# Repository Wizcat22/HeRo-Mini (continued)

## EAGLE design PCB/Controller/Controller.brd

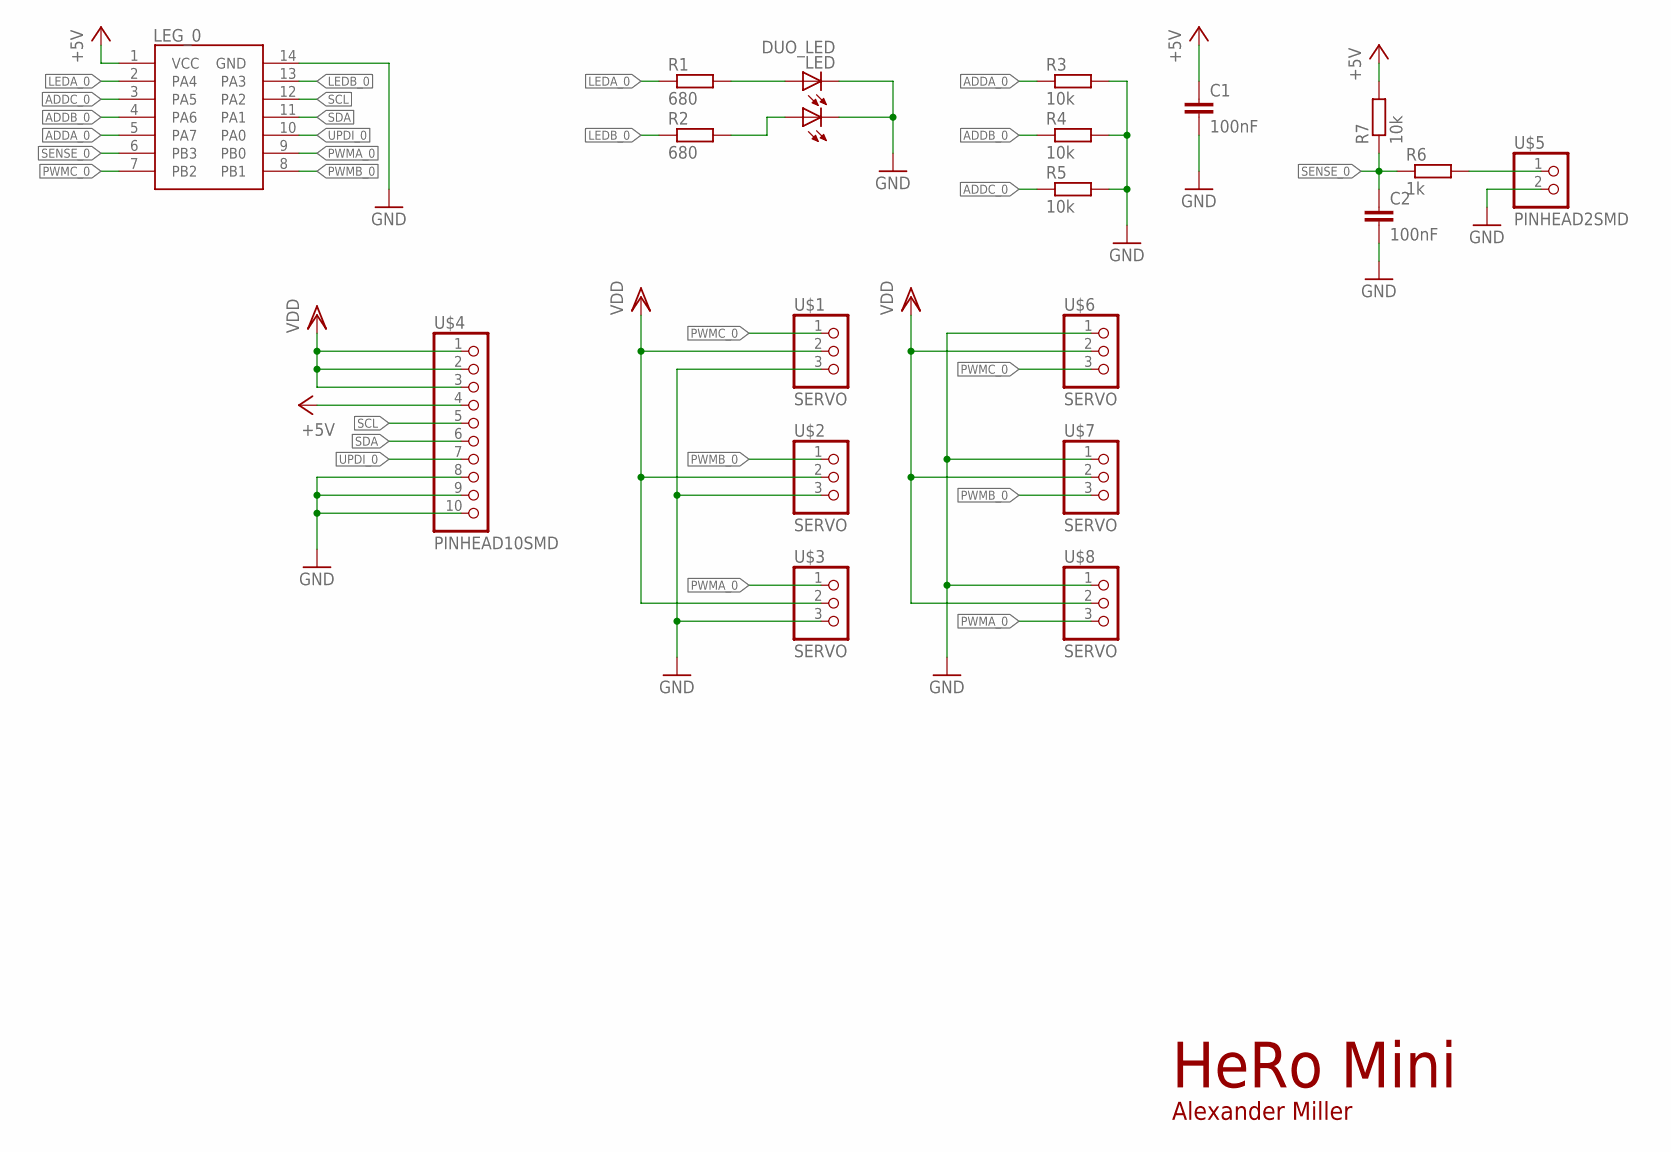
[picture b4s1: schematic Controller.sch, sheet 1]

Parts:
C1, C2: 100nF; C0805
LED: DUO_LED
LEG_0: ATTINY16142; SOIC127P600X175-14
R1, R2: 680; R0805
R3, R4, R5, R7: 10k; R0805
R6: 1k; R0805
U$1, U$2, U$3, U$6, U$7, U$8: SERVO; SL12SMD058
U$4: PINHEAD10SMD; PINHD10SMD
U$5: PINHEAD2SMD; PINHD2SMD

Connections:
+5V: C1.1, LEG_0.1 (VCC), R7.2, U$4.4
ADDA_0: LEG_0.5 (PA7), R3.1
ADDB_0: LEG_0.4 (PA6), R4.1
ADDC_0: LEG_0.3 (PA5), R5.1
GND: C1.2, C2.2, LED.CG, LED.CR, LEG_0.14 (GND), R3.2, R4.2, R5.2, U$1.3, U$2.3, U$3.3, U$4.8, U$4.9, U$4.10, U$5.2, U$6.1, U$7.1, U$8.1
LEDA_0: LEG_0.2 (PA4), R1.1
LEDB_0: LEG_0.13 (PA3), R2.1
unnamed: LED.AG, R1.2
unnamed: LED.AR, R2.2
unnamed: R6.2, U$5.1
PWMA_0: LEG_0.9 (PB0), U$3.1, U$8.3
PWMB_0: LEG_0.8 (PB1), U$2.1, U$7.3
PWMC_0: LEG_0.7 (PB2), U$1.1, U$6.3
SCL: LEG_0.12 (PA2), U$4.5
SDA: LEG_0.11 (PA1), U$4.6
SENSE_0: C2.1, LEG_0.6 (PB3), R6.1, R7.1
UPDI_0: LEG_0.10 (PA0), U$4.7
VDD: U$1.2, U$2.2, U$3.2, U$4.1, U$4.2, U$4.3, U$6.2, U$7.2, U$8.2

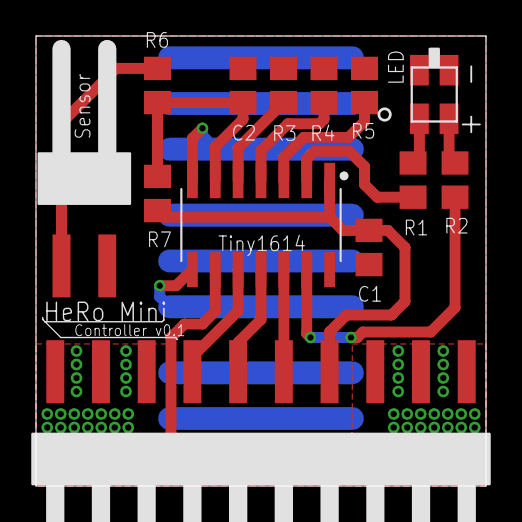
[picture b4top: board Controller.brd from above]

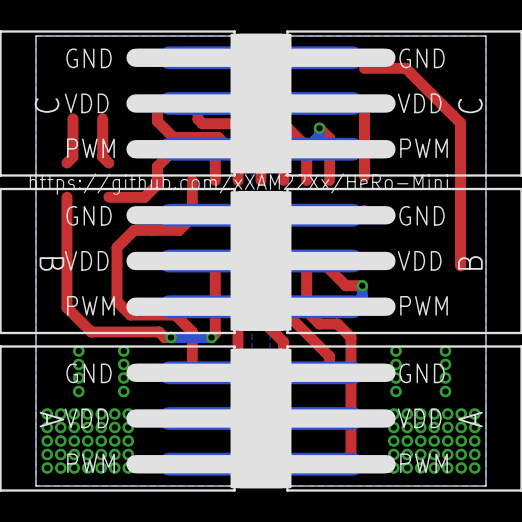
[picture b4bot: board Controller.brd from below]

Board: 2 copper layers, 25.0 x 25.0 mm, 19 parts (6 on the bottom side), 18 nets.

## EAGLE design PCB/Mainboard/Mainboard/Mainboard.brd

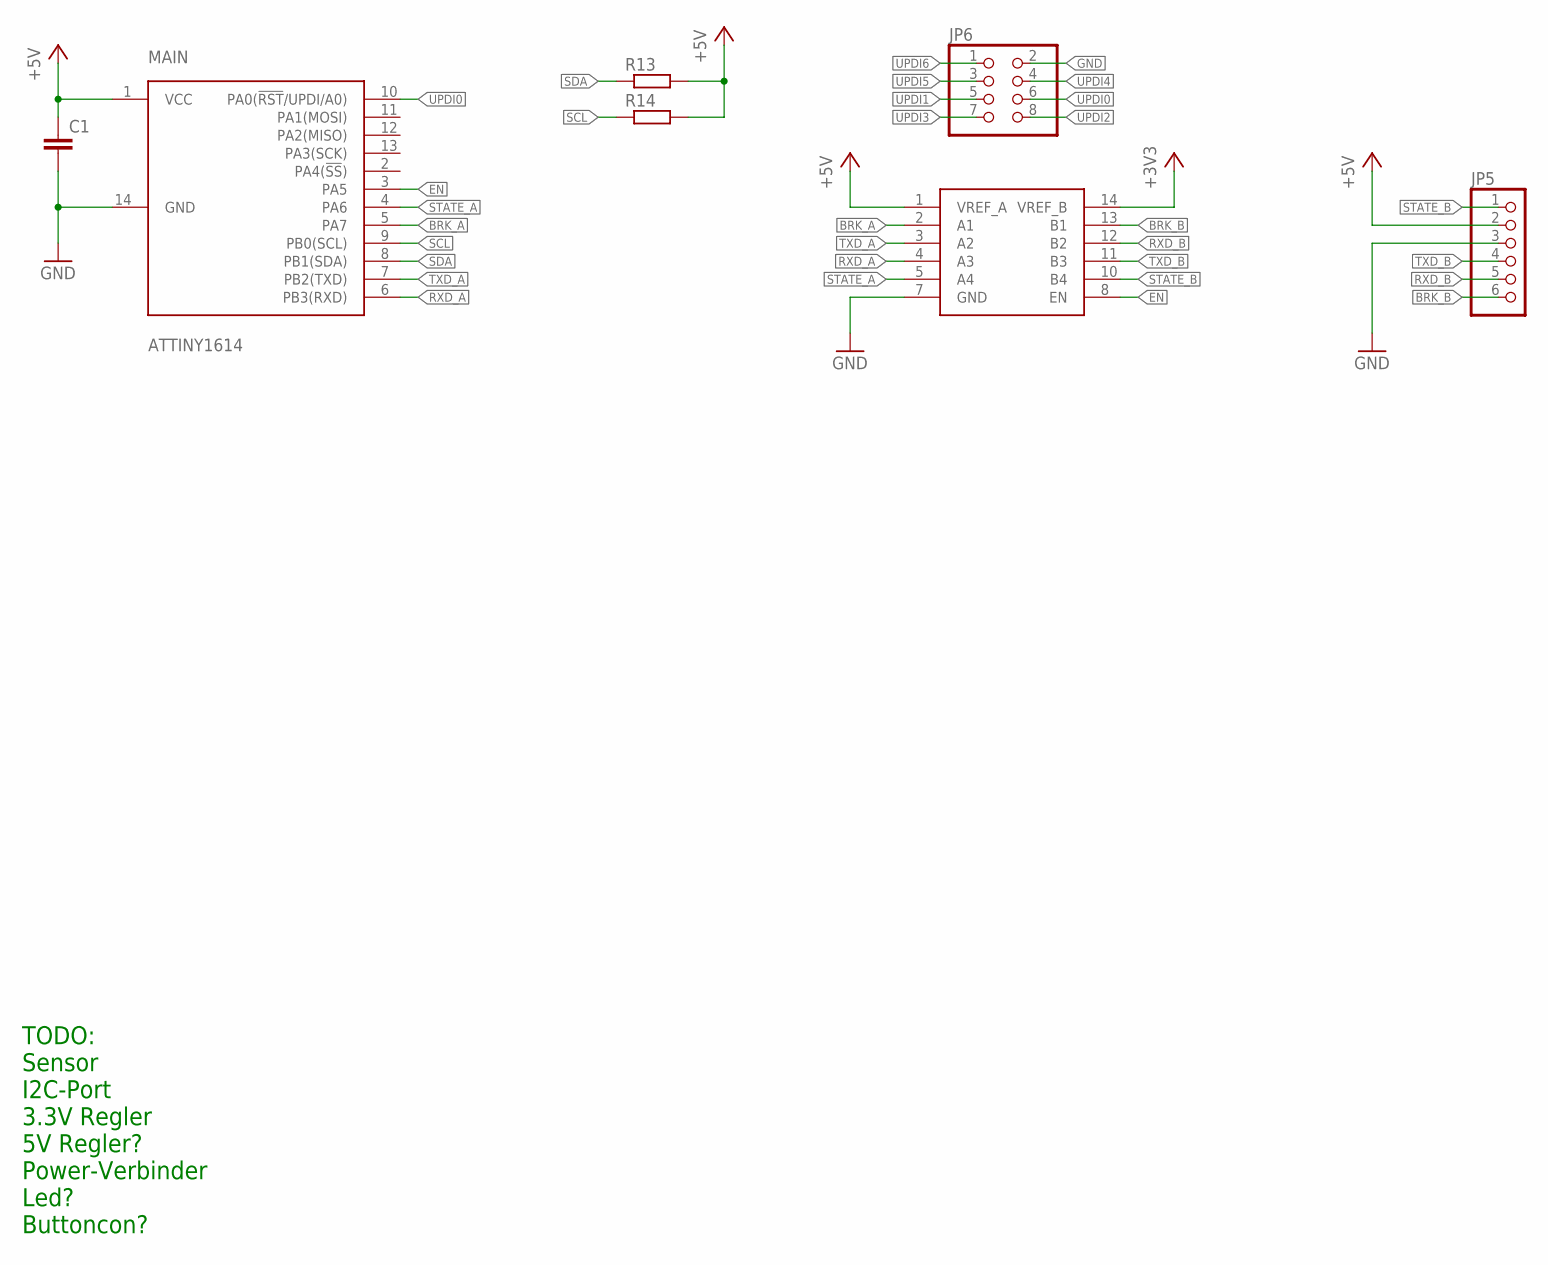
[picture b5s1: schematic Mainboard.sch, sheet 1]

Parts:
C1: C-EUC0805; C0805
JP5: PINHD-1X6; 1X06
JP6: PINHD-2X4; 2X04
MAIN: ATTINY1614; SOIC14
R13, R14: R-EU_R0805; R0805
U$2: LSF0204; TSSOP14

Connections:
+3V3: U$2.14 (VREF_B)
+5V: C1.1, JP5.2, MAIN.1 (VCC), R13.2, R14.2, U$2.1 (VREF_A); also elsewhere on the board
BRK_A: MAIN.5 (PA7), U$2.2 (A1)
BRK_B: JP5.6, U$2.13 (B1)
EN: MAIN.3 (PA5), U$2.8 (EN)
GND: C1.2, JP5.3, JP6.2, MAIN.14 (GND), U$2.7 (GND); also elsewhere on the board
RXD_A: MAIN.6 (PB3(RXD)), U$2.4 (A3)
RXD_B: JP5.5, U$2.12 (B2)
SCL: MAIN.9 (PB0(SCL)), R14.1; also elsewhere on the board
SDA: MAIN.8 (PB1(SDA)), R13.1; also elsewhere on the board
STATE_A: MAIN.4 (PA6), U$2.5 (A4)
STATE_B: JP5.1, U$2.10 (B4)
TXD_A: MAIN.7 (PB2(TXD)), U$2.3 (A2)
TXD_B: JP5.4, U$2.11 (B3)
UPDI0: JP6.6, MAIN.10 (PA0(!RST!/UPDI/A0))
UPDI1: JP6.5; also elsewhere on the board
UPDI2: JP6.8; also elsewhere on the board
UPDI3: JP6.7; also elsewhere on the board
UPDI4: JP6.4; also elsewhere on the board
UPDI5: JP6.3; also elsewhere on the board
UPDI6: JP6.1; also elsewhere on the board

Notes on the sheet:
TODO: Sensor I2C-Port 3.3V Regler 5V Regler? Power-Verbinder Led? Buttoncon?

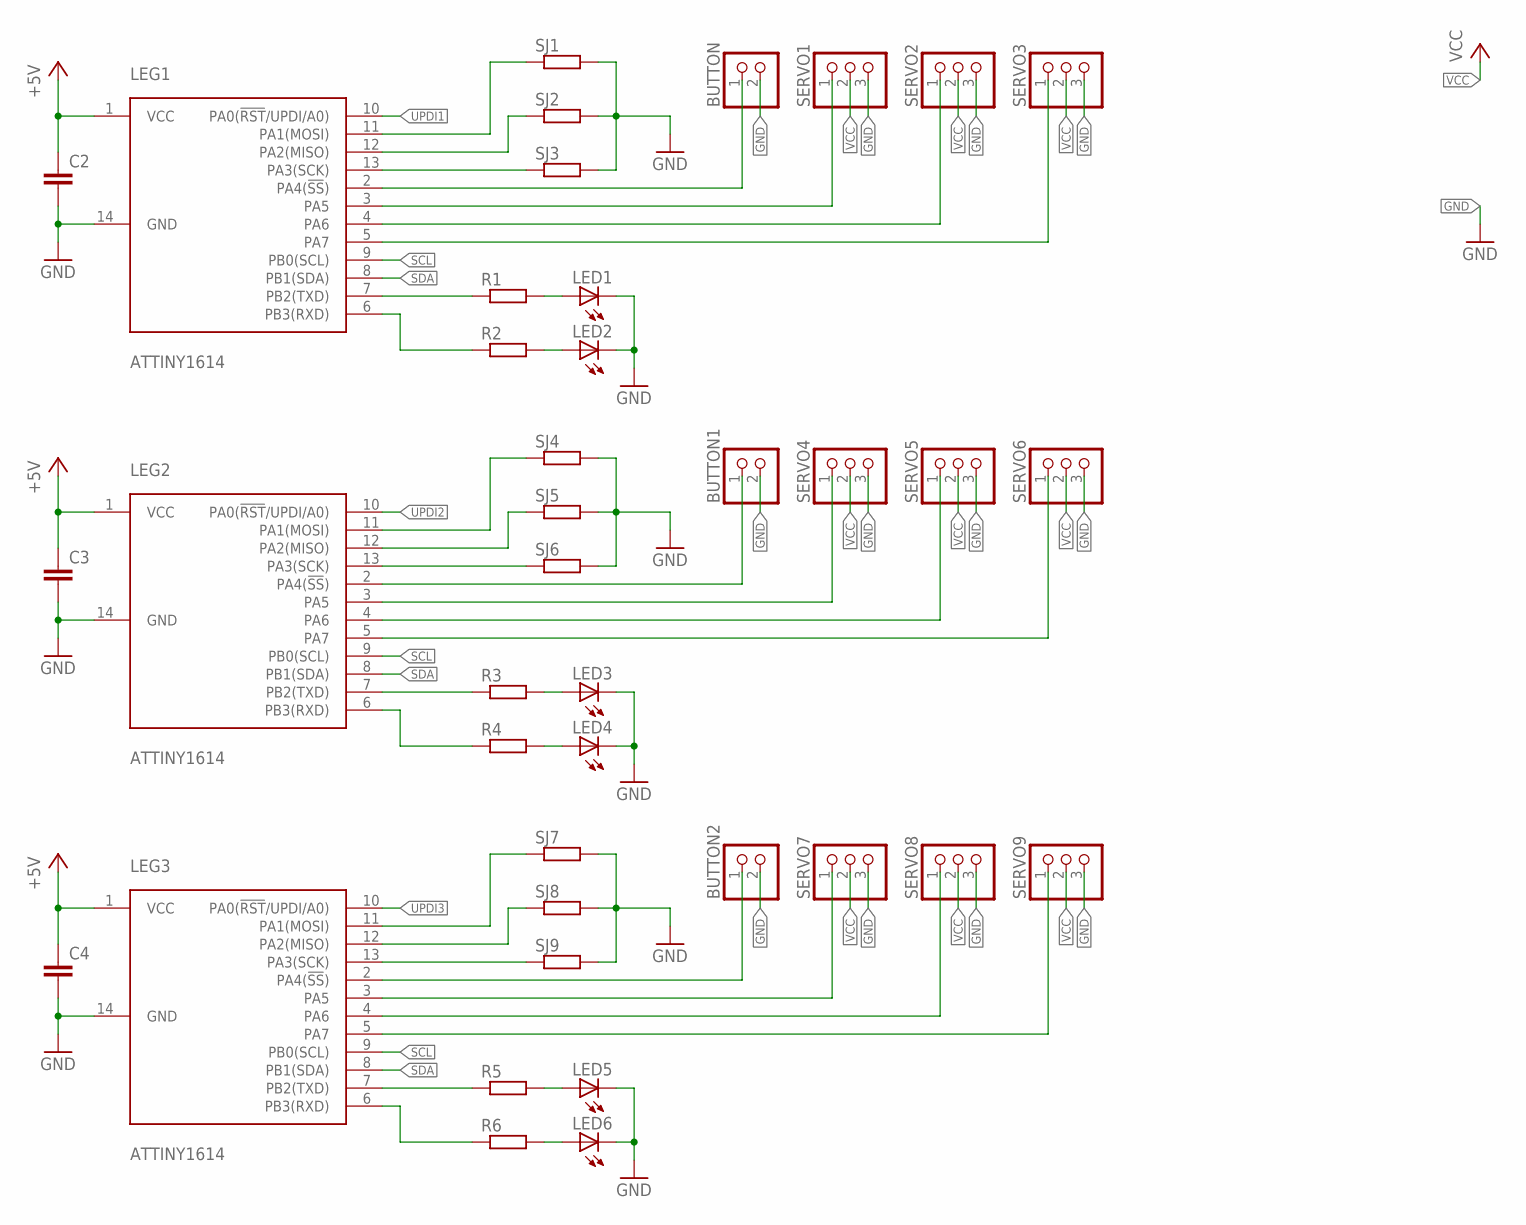
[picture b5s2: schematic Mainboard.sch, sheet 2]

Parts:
BUTTON, BUTTON1, BUTTON2: PINHD-1X2; 1X02
C2, C3, C4: C-EUC0805; C0805
LED1, LED2, LED3, LED4, LED5, LED6: LEDCHIP-LED0805; CHIP-LED0805
LEG1, LEG2, LEG3: ATTINY1614; SOIC14
R1, R2, R3, R4, R5, R6: R-EU_R0805; R0805
SERVO1, SERVO2, SERVO3, SERVO4, SERVO5, SERVO6, SERVO7, SERVO8, SERVO9: PINHD-1X3; 1X03
SJ1, SJ2, SJ3, SJ4, SJ5, SJ6, SJ7, SJ8, SJ9: R-EU_R0402; R0402

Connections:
+5V: C2.1, C3.1, C4.1, LEG1.1 (VCC), LEG2.1 (VCC), LEG3.1 (VCC); also elsewhere on the board
GND: BUTTON.2, BUTTON1.2, BUTTON2.2, C2.2, C3.2, C4.2, LED1.C, LED2.C, LED3.C, LED4.C, LED5.C, LED6.C, LEG1.14 (GND), LEG2.14 (GND), LEG3.14 (GND), SERVO1.3, SERVO2.3, SERVO3.3, SERVO4.3, SERVO5.3, SERVO6.3, SERVO7.3, SERVO8.3, SERVO9.3, SJ1.2, SJ2.2, SJ3.2, SJ4.2, SJ5.2, SJ6.2, SJ7.2, SJ8.2, SJ9.2; also elsewhere on the board
unnamed: LEG1.7 (PB2(TXD)), R1.1
unnamed: LEG1.6 (PB3(RXD)), R2.1
unnamed: LEG1.11 (PA1(MOSI)), SJ1.1
unnamed: LEG1.12 (PA2(MISO)), SJ2.1
unnamed: LEG1.13 (PA3(SCK)), SJ3.1
unnamed: LED1.A, R1.2
unnamed: LED2.A, R2.2
unnamed: BUTTON.1, LEG1.2 (PA4(!SS!))
unnamed: LEG1.3 (PA5), SERVO1.1
unnamed: LEG1.4 (PA6), SERVO2.1
unnamed: LED3.A, R3.2
unnamed: LEG1.5 (PA7), SERVO3.1
unnamed: LED4.A, R4.2
unnamed: LEG2.7 (PB2(TXD)), R3.1
unnamed: LEG2.6 (PB3(RXD)), R4.1
unnamed: LEG2.11 (PA1(MOSI)), SJ4.1
unnamed: LEG2.12 (PA2(MISO)), SJ5.1
unnamed: LEG2.13 (PA3(SCK)), SJ6.1
unnamed: BUTTON1.1, LEG2.2 (PA4(!SS!))
unnamed: LEG2.3 (PA5), SERVO4.1
unnamed: LEG2.4 (PA6), SERVO5.1
unnamed: LEG2.5 (PA7), SERVO6.1
unnamed: LED5.A, R5.2
unnamed: LED6.A, R6.2
unnamed: LEG3.7 (PB2(TXD)), R5.1
unnamed: LEG3.6 (PB3(RXD)), R6.1
unnamed: LEG3.11 (PA1(MOSI)), SJ7.1
unnamed: LEG3.12 (PA2(MISO)), SJ8.1
unnamed: LEG3.13 (PA3(SCK)), SJ9.1
unnamed: BUTTON2.1, LEG3.2 (PA4(!SS!))
unnamed: LEG3.3 (PA5), SERVO7.1
unnamed: LEG3.4 (PA6), SERVO8.1
unnamed: LEG3.5 (PA7), SERVO9.1
SCL: LEG1.9 (PB0(SCL)), LEG2.9 (PB0(SCL)), LEG3.9 (PB0(SCL)); also elsewhere on the board
SDA: LEG1.8 (PB1(SDA)), LEG2.8 (PB1(SDA)), LEG3.8 (PB1(SDA)); also elsewhere on the board
UPDI1: LEG1.10 (PA0(!RST!/UPDI/A0)); also elsewhere on the board
UPDI2: LEG2.10 (PA0(!RST!/UPDI/A0)); also elsewhere on the board
UPDI3: LEG3.10 (PA0(!RST!/UPDI/A0)); also elsewhere on the board
VCC: SERVO1.2, SERVO2.2, SERVO3.2, SERVO4.2, SERVO5.2, SERVO6.2, SERVO7.2, SERVO8.2, SERVO9.2

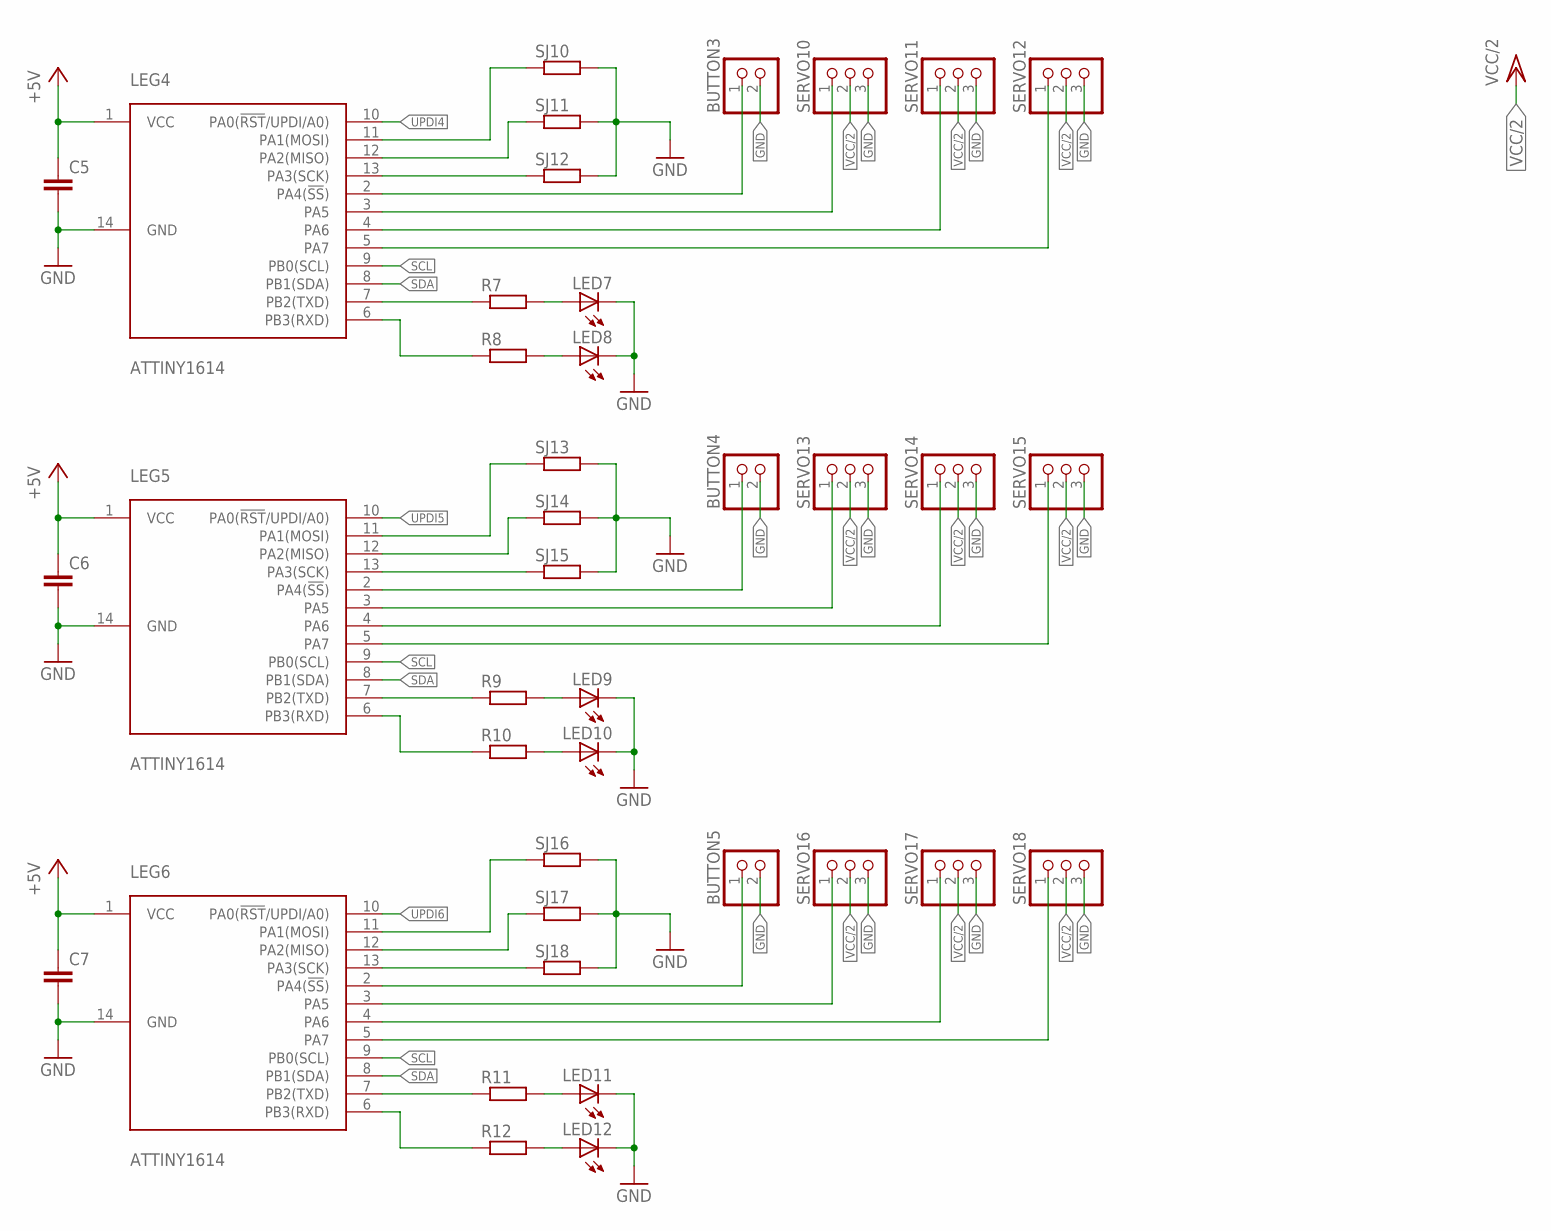
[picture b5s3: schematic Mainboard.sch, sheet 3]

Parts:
BUTTON3, BUTTON4, BUTTON5: PINHD-1X2; 1X02
C5, C6, C7: C-EUC0805; C0805
LED7, LED8, LED9, LED10, LED11, LED12: LEDCHIP-LED0805; CHIP-LED0805
LEG4, LEG5, LEG6: ATTINY1614; SOIC14
R7, R8, R9, R10, R11, R12: R-EU_R0805; R0805
SERVO10, SERVO11, SERVO12, SERVO13, SERVO14, SERVO15, SERVO16, SERVO17, SERVO18: PINHD-1X3; 1X03
SJ10, SJ11, SJ12, SJ13, SJ14, SJ15, SJ16, SJ17, SJ18: R-EU_R0402; R0402

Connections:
+5V: C5.1, C6.1, C7.1, LEG4.1 (VCC), LEG5.1 (VCC), LEG6.1 (VCC); also elsewhere on the board
GND: BUTTON3.2, BUTTON4.2, BUTTON5.2, C5.2, C6.2, C7.2, LED7.C, LED8.C, LED9.C, LED10.C, LED11.C, LED12.C, LEG4.14 (GND), LEG5.14 (GND), LEG6.14 (GND), SERVO10.3, SERVO11.3, SERVO12.3, SERVO13.3, SERVO14.3, SERVO15.3, SERVO16.3, SERVO17.3, SERVO18.3, SJ10.2, SJ11.2, SJ12.2, SJ13.2, SJ14.2, SJ15.2, SJ16.2, SJ17.2, SJ18.2; also elsewhere on the board
unnamed: LED7.A, R7.2
unnamed: LED8.A, R8.2
unnamed: LEG4.7 (PB2(TXD)), R7.1
unnamed: LEG4.6 (PB3(RXD)), R8.1
unnamed: LEG4.11 (PA1(MOSI)), SJ10.1
unnamed: LEG4.12 (PA2(MISO)), SJ11.1
unnamed: LEG4.13 (PA3(SCK)), SJ12.1
unnamed: BUTTON3.1, LEG4.2 (PA4(!SS!))
unnamed: LEG4.3 (PA5), SERVO10.1
unnamed: LEG4.4 (PA6), SERVO11.1
unnamed: LEG4.5 (PA7), SERVO12.1
unnamed: LED9.A, R9.2
unnamed: LED10.A, R10.2
unnamed: LEG5.7 (PB2(TXD)), R9.1
unnamed: LEG5.6 (PB3(RXD)), R10.1
unnamed: LEG5.11 (PA1(MOSI)), SJ13.1
unnamed: LEG5.12 (PA2(MISO)), SJ14.1
unnamed: LEG5.13 (PA3(SCK)), SJ15.1
unnamed: BUTTON4.1, LEG5.2 (PA4(!SS!))
unnamed: LEG5.3 (PA5), SERVO13.1
unnamed: LEG5.4 (PA6), SERVO14.1
unnamed: LEG5.5 (PA7), SERVO15.1
unnamed: LED11.A, R11.2
unnamed: LED12.A, R12.2
unnamed: LEG6.7 (PB2(TXD)), R11.1
unnamed: LEG6.6 (PB3(RXD)), R12.1
unnamed: LEG6.11 (PA1(MOSI)), SJ16.1
unnamed: LEG6.12 (PA2(MISO)), SJ17.1
unnamed: LEG6.13 (PA3(SCK)), SJ18.1
unnamed: BUTTON5.1, LEG6.2 (PA4(!SS!))
unnamed: LEG6.3 (PA5), SERVO16.1
unnamed: LEG6.4 (PA6), SERVO17.1
unnamed: LEG6.5 (PA7), SERVO18.1
SCL: LEG4.9 (PB0(SCL)), LEG5.9 (PB0(SCL)), LEG6.9 (PB0(SCL)); also elsewhere on the board
SDA: LEG4.8 (PB1(SDA)), LEG5.8 (PB1(SDA)), LEG6.8 (PB1(SDA)); also elsewhere on the board
UPDI4: LEG4.10 (PA0(!RST!/UPDI/A0)); also elsewhere on the board
UPDI5: LEG5.10 (PA0(!RST!/UPDI/A0)); also elsewhere on the board
UPDI6: LEG6.10 (PA0(!RST!/UPDI/A0)); also elsewhere on the board
VCC/2: SERVO10.2, SERVO11.2, SERVO12.2, SERVO13.2, SERVO14.2, SERVO15.2, SERVO16.2, SERVO17.2, SERVO18.2

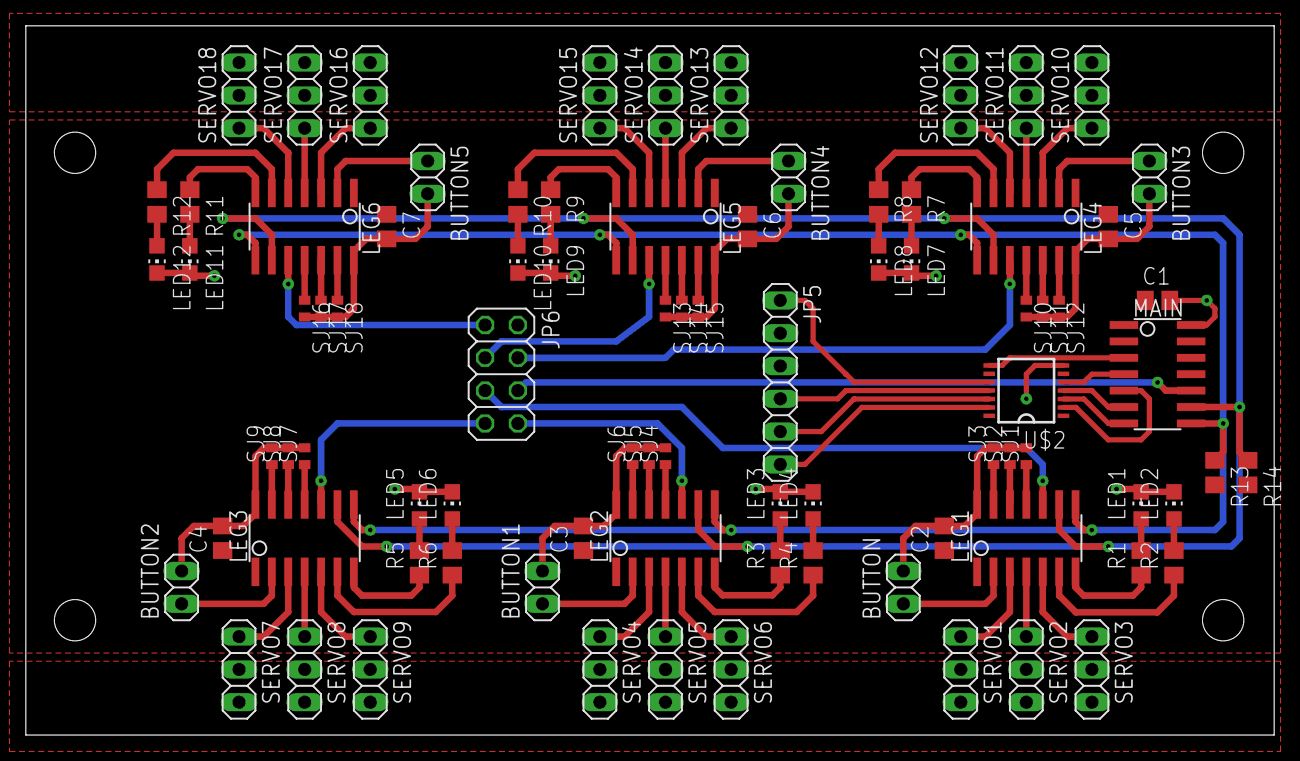
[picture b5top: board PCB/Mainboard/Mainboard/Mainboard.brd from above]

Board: 2 copper layers, 96.7 x 54.9 mm, 85 parts (0 on the bottom side), 88 nets.

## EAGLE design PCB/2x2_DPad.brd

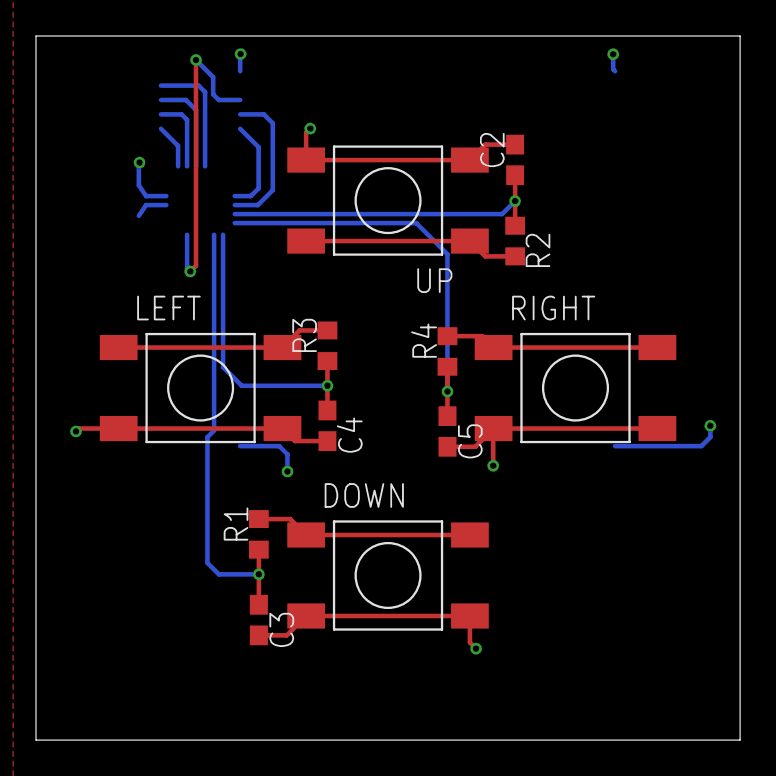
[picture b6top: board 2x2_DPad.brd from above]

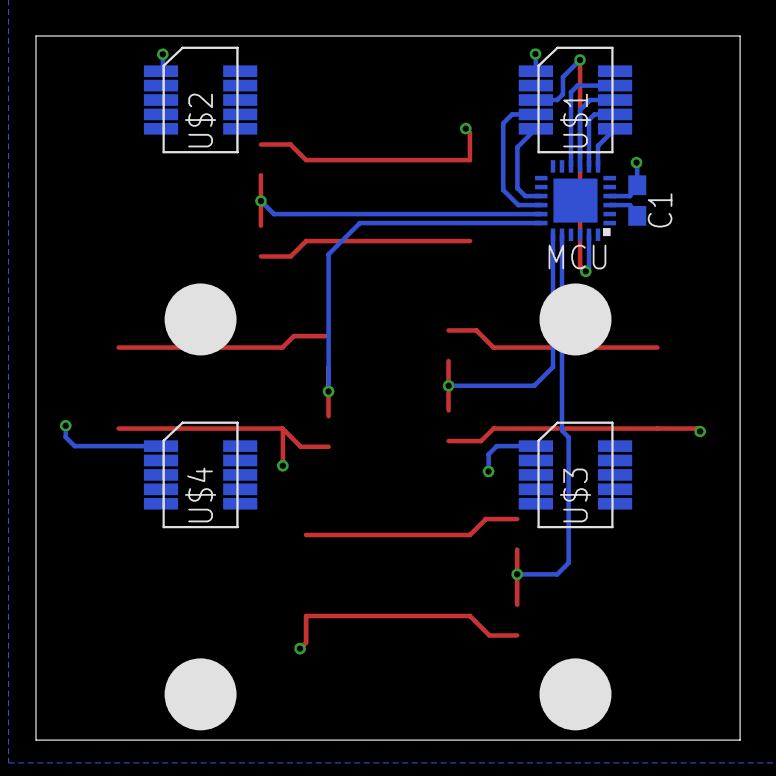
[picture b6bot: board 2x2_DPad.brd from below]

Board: 2 copper layers, 39.1 x 39.1 mm, 18 parts (6 on the bottom side), 17 nets.

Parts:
C1: 100nF; C0603
C2, C3, C4, C5: 20nF; C0603
DOWN: TASTER
LEFT: TASTER
MCU: ATTINY1614/16/17; QFN24-4X4
R1, R2, R3, R4: 1k; R0603
RIGHT: TASTER
U$1, U$2, U$3, U$4: MOLEX-STACKINGHEADER; 53307-1071
UP: TASTER

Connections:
+5V: C1.1, MCU.4, U$1.P$1, U$2.P$1, U$3.P$1, U$4.P$1
ADD0: MCU.7, U$1.P$6
ADD1: MCU.8, U$1.P$7
ADD2: MCU.9, U$1.P$8
ADD3: MCU.10, U$1.P$9
DOWN: C3.1, MCU.20, R1.1
GND: C1.2, C2.2, C3.2, C4.2, C5.2, DOWN.B0, DOWN.B1, LEFT.B0, LEFT.B1, MCU.3, RIGHT.B0, RIGHT.B1, U$1.P$10, U$2.P$10, U$3.P$10, U$4.P$10, UP.B0, UP.B1
LEFT: C4.1, MCU.19, R3.1
unnamed: DOWN.A0, DOWN.A1, R1.2
unnamed: LEFT.A0, LEFT.A1, R3.2
unnamed: R2.2, UP.A0, UP.A1
unnamed: R4.2, RIGHT.A0, RIGHT.A1
RIGHT: C5.1, MCU.18, R4.1
SCL: MCU.16, U$1.P$4
SDA: MCU.15, U$1.P$5
UP: C2.1, MCU.17, R2.1
UPDI: MCU.23, U$1.P$3

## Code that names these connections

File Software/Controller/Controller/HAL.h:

/*
* HAL.h
*
* Created: 13.06.2018 23:04:03
*  Author: alex-
*/

//PIN DEFINITION
//1-VCC
//2-PA4-LEDA
//3-PA5-ADDC
//4-PA6-ADDB
//5-PA7-ADDA
//6-PB3-SENSE
//7-PB2-PWMC
//8-PB1-PWMB
//9-PB0-PWMA
//10-PA0-UPDI
//11-PA1-SDA
//12-PA2-SCL
//13-PA3-LEDB
//14-GND



#ifndef HAL_H_
#define HAL_H_

#define F_CPU 20000000
#define HIGH 1
#define LOW 0
#define LEDA PIN4_bp
#define LEDB PIN3_bp
#define SENSE PIN3_bm
#define PWMA 0
#define PWMB 1
#define PWMC 2

#define ADDA PIN7_bp
#define ADDB PIN6_bp
#define ADDC PIN5_bp
#define I2C_ACK TWI_SCMD_RESPONSE_gc
#define I2C_TCOMP TWI_SCMD_COMPTRANS_gc
#define F_SERVO 50
#define PERIOD_TIMER ((F_CPU) / ((uint16_t)(F_SERVO)*8))


#include <avr/io.h>
#include <util/delay.h>
#include <avr/wdt.h>

void init_hw(void);
void init_led(void);
void init_pwm(void);
void init_i2c(void);
void init_sense(void);
void led_write(uint8_t led, uint8_t state);
uint8_t sense_read(void);
void pwm_write(uint8_t channel,uint16_t value);
uint8_t i2c_read_byte(void);
void i2c_write_byte(uint8_t data);
void i2c_write_response(uint8_t response);

#endif /* HAL_H_ */

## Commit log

2017-09-27 New Parts
2017-10-29 Minor changes
2017-11-28 Initial upload
2017-12-18 Added missing leg controller + layout
2017-12-18 Finished layout for current circuit
2018-01-05 Adjusted all parts, added screws and nuts
2018-01-05 Added 4 holes
2018-01-24 New Leg
2018-03-15 Release
2018-03-30 Redesign
2018-04-12 Finished Servocontroller design
2018-05-01 Minor changes in controller, new mainboard
2018-05-01 Changed PCB size to 25mmx25mm
2018-05-02 WIP Mainboard design
2018-06-13 Initial Code upload
2018-06-14 Implemented all HAL functions
    Tested: led,pwm,sense
    TODO: test i2c communication
2018-06-17 Added servo functions
2018-06-21 implemented "servo_write_deg()"
2018-06-24 New classes for every component (Led, Sensor, Servo)
2018-07-13 Minor Redesign
    Replace ESP32 Eval board with own design
2018-07-19 added new parts, added all signals
2018-07-20 minor adjustments, finished routing
2018-07-20 Added sketch for pcb placement
2018-07-30 finalised routing, added 3D-Models
2018-07-30 New Design, added PCBs (and Placeholders)
2018-08-02 Tested I2C communication
2018-08-03 Upload Transmitter/Receiver code
2018-08-03 Added I2C test
2018-08-07 Ported code from Hexapod - Untested
2018-08-07 upload controller software (get gamepad data, send data to transmitter)
2018-09-27 Bug fixes, added X-Formation
2018-10-29 Initial Upload of new Leg Prototype
2018-11-12 Upload Gamepad
2018-11-25 Motor-Control test project
    Testing QDEC and PID
